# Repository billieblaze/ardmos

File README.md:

ardmos
======

an Arduino Musical Device Operating System

So, I've got this idea for a totally modular synth / controller / whatever environment.   A master ATMega runs an event driven framework and manages any time sensitive operations.   It delegates tasks to a series of "modules" like Digitial IO, Analog IO, MIDI, Matrix LED, etc. Rather then connecting the master straight to a shift register chain, or some other peripherals,  the functionality would be controlled by an i2c ATtiny slave.   

Why would I want to do this?  Well, I've got several musical related projects (Midi sequencer, wavetable oscillator, midi controllers) and I'd like to reign in the codebase a little.  Each project has many similarities that could easily be abstracted.  I feel the advantages are huge for a few reasons:   

1) UI and other long running tasks don't tie up the more crucial time sensitive bits
2) Modules could become their own standalone gizmos or could be interconnected in almost limitless ways

As with many of my projects, I will be standing on the shoulders of giants and utilizing well documented open source libraries and tools and will keep track of that info here as well. 

Proposed Core functionality:
 - Event Driven framework or RTOS
 - MIDI IO with thru / clock sync / clock gen
 - Bootload slaves via I2c using TinySafeBoot (http://jtxp.org/tech/tinysafeboot_en.htm)
 - Allow configuration of slave address / role 

Modules will have an address and a corresponding role.   A simple messaging setup should allow a few bits
to delegate any task and value from the core to the slave.  

In Progress: 
	SuperIO
	- RGB LED Matrix (standard matrix or sparkfun rgb button pad) - TLC5940 + 74hc164 + tlc59213 for led  and 74hc165 for keypad in  
      I'd like to look at the monome protocol for communicating with it since thats already defined, but the device should be able to be independant of pc! 
	- Digital In (button / encoders) 
	- Digital Out (led / trigger / etc)

Other Proposed modules for V1:
	- Analog In  (rot ary pots, audio, cv, etc)  -- todo: select mux
	- Analog Out  (i2c dac, audio / cv)   -- Max525/5250?  
	- I2c text and graphical lcds - these are probably going to wind up being attached to the master, but i've had i2c led related problems in some of my other sketches
	- communication with other platforms (arm / propeller / etc)

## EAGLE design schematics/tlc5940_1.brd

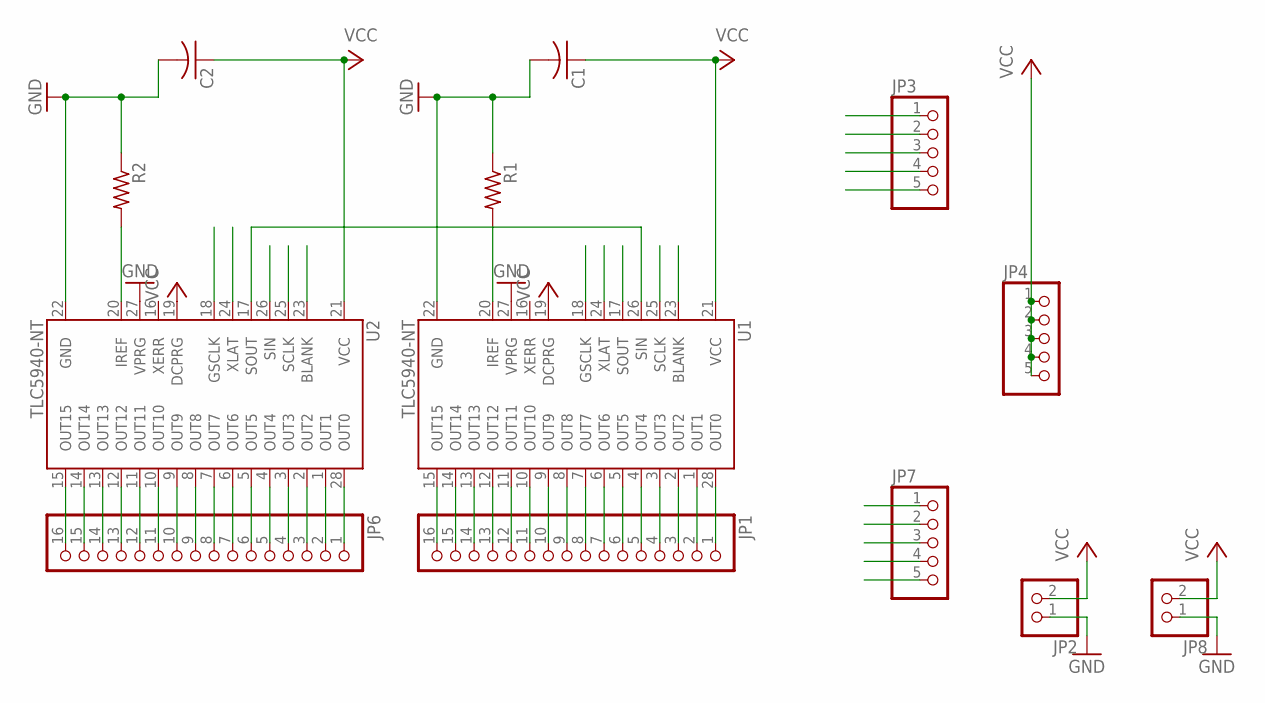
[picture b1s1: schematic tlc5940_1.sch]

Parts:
C1, C2: C-US025-024X044; C025-024X044
JP1, JP6: PINHD-1X16; 1X16
JP2, JP8: PINHD-1X2; 1X02
JP3, JP4, JP7: PINHD-1X5; 1X05
R1, R2: R-US_0613/5V; P0613V
U1, U2: TLC5940-NT; DIL28-3

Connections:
BLANK: JP3.5, JP7.5, U1.23 (BLANK), U2.23 (BLANK)
GND: C1.2, C2.2, JP2.1, JP8.1, R1.1, R2.1, U1.22 (GND), U1.27 (VPRG), U2.22 (GND), U2.27 (VPRG)
GSCLK: JP3.1, JP7.1, U1.18 (GSCLK), U2.18 (GSCLK)
unnamed: JP1.1, U1.28 (OUT0)
unnamed: JP1.2, U1.1 (OUT1)
unnamed: JP1.3, U1.2 (OUT2)
unnamed: JP1.4, U1.3 (OUT3)
unnamed: JP1.5, U1.4 (OUT4)
unnamed: JP1.6, U1.5 (OUT5)
unnamed: JP1.7, U1.6 (OUT6)
unnamed: JP1.8, U1.7 (OUT7)
unnamed: JP1.9, U1.8 (OUT8)
unnamed: JP1.10, U1.9 (OUT9)
unnamed: JP1.11, U1.10 (OUT10)
unnamed: JP1.12, U1.11 (OUT11)
unnamed: JP1.13, U1.12 (OUT12)
unnamed: JP1.14, U1.13 (OUT13)
unnamed: JP1.15, U1.14 (OUT14)
unnamed: JP1.16, U1.15 (OUT15)
unnamed: R1.2, U1.20 (IREF)
unnamed: U1.26 (SIN), U2.17 (SOUT)
unnamed: JP6.1, U2.28 (OUT0)
unnamed: JP6.2, U2.1 (OUT1)
unnamed: JP6.3, U2.2 (OUT2)
unnamed: JP6.4, U2.3 (OUT3)
unnamed: JP6.5, U2.4 (OUT4)
unnamed: JP6.6, U2.5 (OUT5)
unnamed: JP6.7, U2.6 (OUT6)
unnamed: JP6.8, U2.7 (OUT7)
unnamed: JP6.9, U2.8 (OUT8)
unnamed: JP6.10, U2.9 (OUT9)
unnamed: JP6.11, U2.10 (OUT10)
unnamed: JP6.12, U2.11 (OUT11)
unnamed: JP6.13, U2.12 (OUT12)
unnamed: JP6.14, U2.13 (OUT13)
unnamed: JP6.15, U2.14 (OUT14)
unnamed: JP6.16, U2.15 (OUT15)
unnamed: R2.2, U2.20 (IREF)
SCLK: JP3.4, JP7.4, U1.25 (SCLK), U2.25 (SCLK)
SIN: JP3.3, U2.26 (SIN)
SOUT: JP7.3, U1.17 (SOUT)
VCC: C1.1, C2.1, JP2.2, JP4.1, JP4.2, JP4.3, JP4.4, JP4.5, JP8.2, U1.19 (DCPRG), U1.21 (VCC), U2.19 (DCPRG), U2.21 (VCC)
XLAT: JP3.2, JP7.2, U1.24 (XLAT), U2.24 (XLAT)

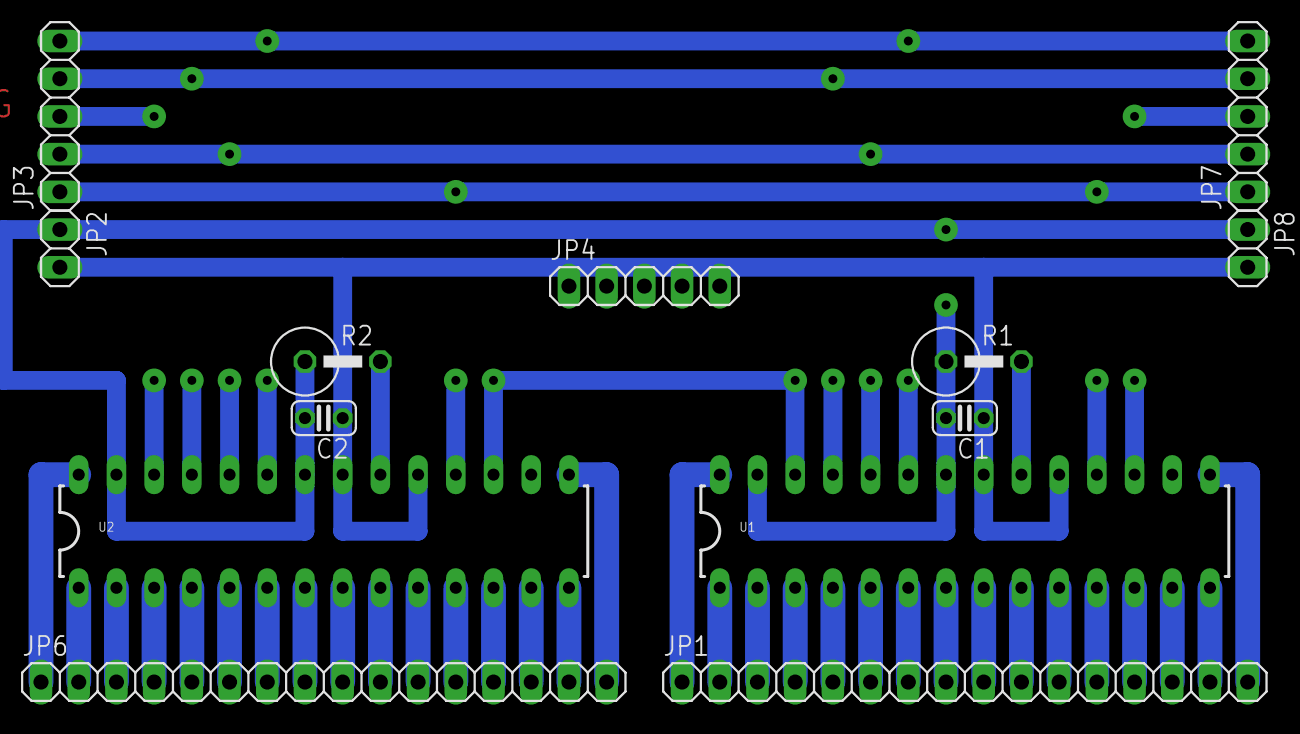
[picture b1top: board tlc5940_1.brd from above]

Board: 2 copper layers, 13 parts (0 on the bottom side), 43 nets.

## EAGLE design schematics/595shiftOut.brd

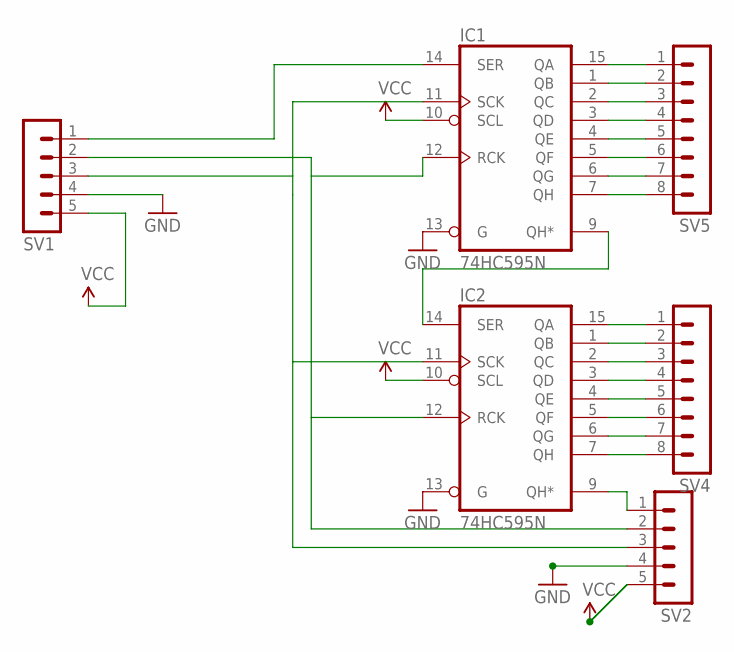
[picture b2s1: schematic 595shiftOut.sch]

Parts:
IC1, IC2: 74HC595N; DIL16
SV1, SV2: MA05-1
SV4, SV5: MA08-1

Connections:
GND: IC1.8 (GND), IC1.13 (G), IC2.8 (GND), IC2.13 (G), SV1.4, SV2.4
unnamed: IC1.14 (SER), SV1.1
unnamed: IC1.12 (RCK), IC2.12 (RCK), SV1.2, SV2.2
unnamed: IC1.11 (SCK), IC2.11 (SCK), SV1.3, SV2.3
unnamed: IC2.15 (QA), SV4.1
unnamed: IC2.1 (QB), SV4.2
unnamed: IC2.2 (QC), SV4.3
unnamed: IC2.3 (QD), SV4.4
unnamed: IC2.4 (QE), SV4.5
unnamed: IC2.5 (QF), SV4.6
unnamed: IC2.6 (QG), SV4.7
unnamed: IC2.7 (QH), SV4.8
unnamed: IC1.15 (QA), SV5.1
unnamed: IC1.1 (QB), SV5.2
unnamed: IC1.2 (QC), SV5.3
unnamed: IC1.3 (QD), SV5.4
unnamed: IC1.4 (QE), SV5.5
unnamed: IC1.5 (QF), SV5.6
unnamed: IC1.6 (QG), SV5.7
unnamed: IC1.7 (QH), SV5.8
unnamed: IC1.9 (QH*), IC2.14 (SER)
unnamed: IC2.9 (QH*), SV2.1
VCC: IC1.10 (SCL), IC1.16 (VCC), IC2.10 (SCL), IC2.16 (VCC), SV1.5, SV2.5

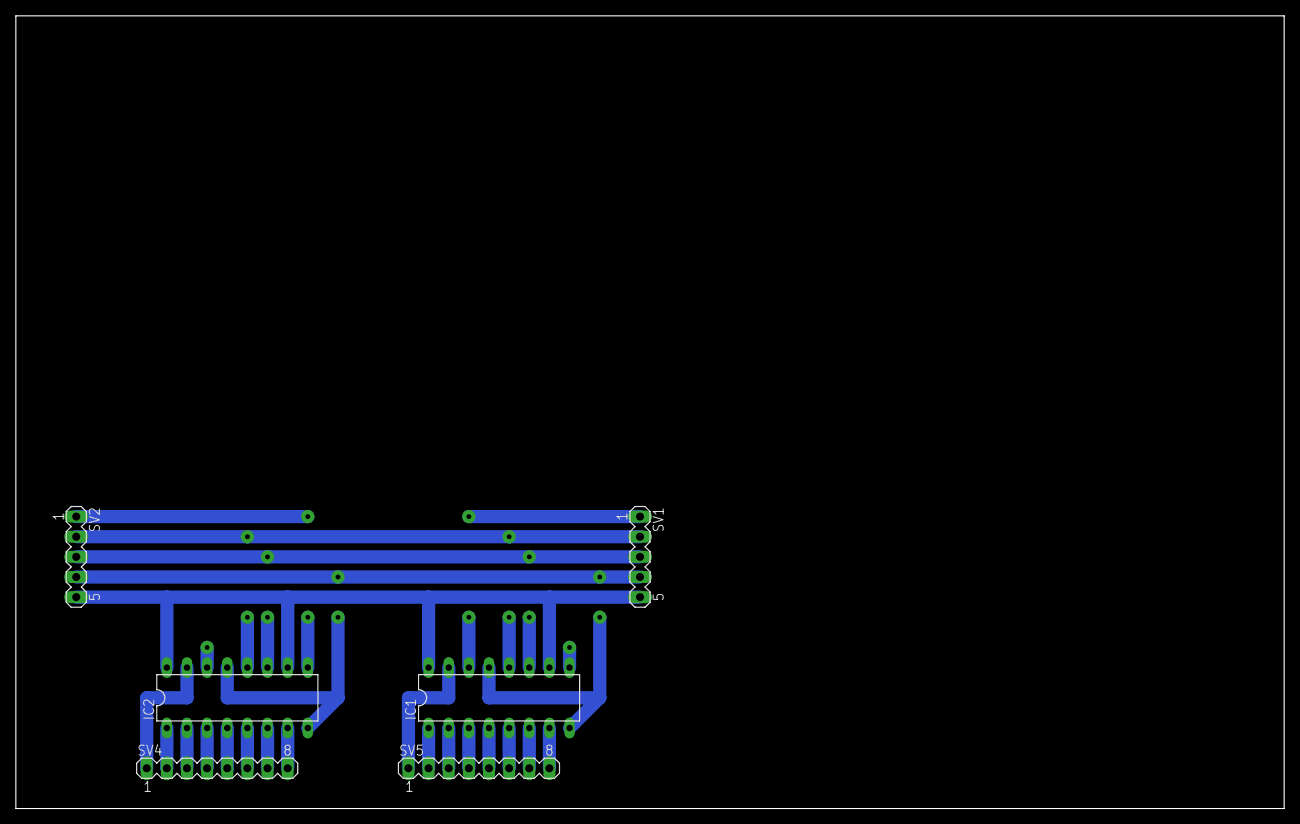
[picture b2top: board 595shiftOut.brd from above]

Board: 2 copper layers, 160.0 x 100.0 mm, 6 parts (0 on the bottom side), 23 nets.

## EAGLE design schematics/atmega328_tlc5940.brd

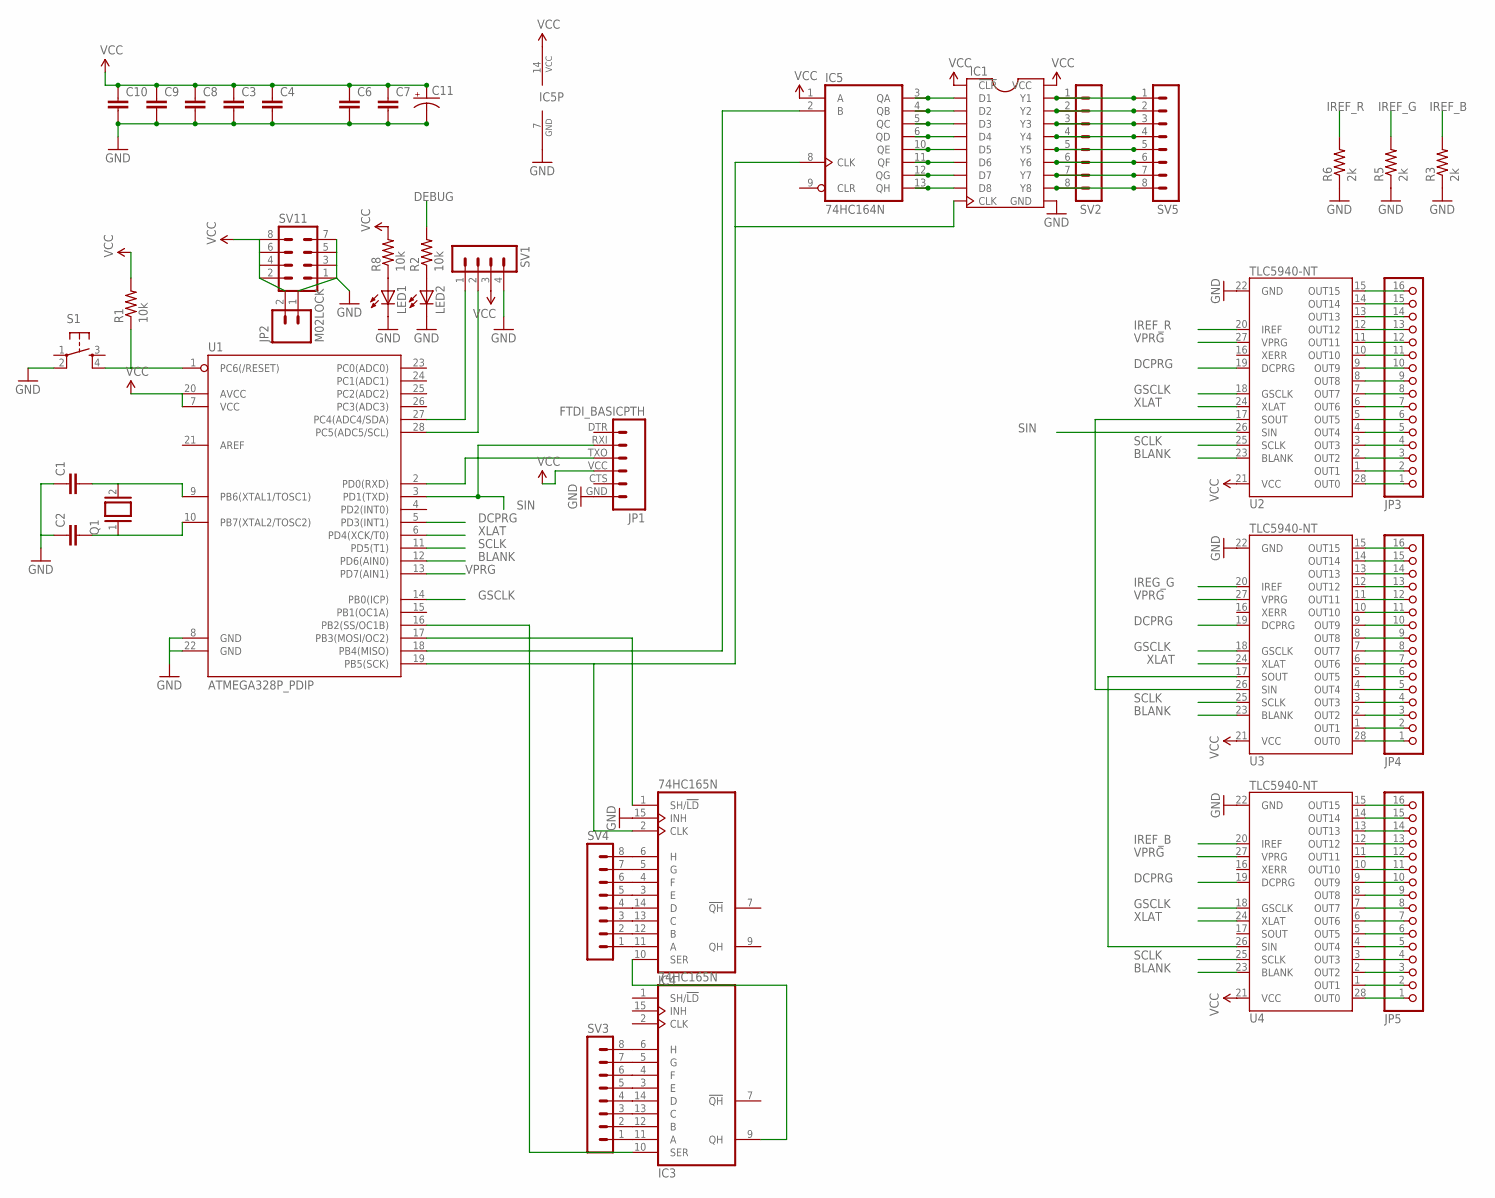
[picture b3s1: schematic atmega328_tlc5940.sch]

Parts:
C1, C2, C3, C4, C6, C7, C8, C9, C10: CAPEZ; CAP-PTH-SMALLEZ
C11: CPOL-USE3.5-8; E3,5-8
IC1: IC-PACKAGE_DIL20S; IC-PACKAGE_SOCKET-20
IC3, IC4: 74HC165N; DIL16
IC5: 74HC164N; DIL14
JP1: FTDI_BASICPTH; FTDI_BASIC
JP2: M02LOCK; 1X02_LOCK
JP3, JP4, JP5: PINHD-1X16; 1X16
LED1, LED2: LED5MM
Q1: XTAL/S; QS
R1, R2, R8: 10k; AXIAL-0.3-KIT
R3, R5, R6: 2k; AXIAL-0.3-KIT
S1: TAC_SWITCHPTH; TACTILE-PTH
SV1: MA04-1
SV2, SV3, SV4, SV5: MA08-1
SV11: MA04-2
U1: ATMEGA328P_PDIP; DIL28-3
U2, U3, U4: TLC5940-NT; DIL28-3

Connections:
BLANK: U1.12 (PD6(AIN0)), U2.23 (BLANK), U3.23 (BLANK), U4.23 (BLANK)
DCPRG: U1.5 (PD3(INT1)), U2.19 (DCPRG), U3.19 (DCPRG), U4.19 (DCPRG)
DEBUG: R2.P$2 (2)
GND: C1.1, C2.1, C3.2, C4.2, C6.2, C7.2, C8.2, C9.2, C10.2, C11.-, IC1.11 (GND), IC3.8 (GND), IC4.8 (GND), IC4.15 (INH), IC5.7 (GND), JP1.GND (6), JP2.1, LED1.K (C), LED2.K (C), R3.P$1 (1), R5.P$1 (1), R6.P$1 (1), S1.2, SV1.4, SV11.1, SV11.3, SV11.5, SV11.7, U1.8 (GND), U1.22 (GND), U2.22 (GND), U3.22 (GND), U4.22 (GND)
GSCLK: U1.14 (PB0(ICP)), U2.18 (GSCLK), U3.18 (GSCLK), U4.18 (GSCLK)
IREF_B: R3.P$2 (2), U4.20 (IREF)
IREF_G: R5.P$2 (2)
IREF_R: R6.P$2 (2), U2.20 (IREF)
IREG_G: U3.20 (IREF)
unnamed: R1.P$1 (1), S1.4, U1.1 (PC6(/RESET))
unnamed: C1.2, Q1.2, U1.9 (PB6(XTAL1/TOSC1))
unnamed: C2.2, Q1.1, U1.10 (PB7(XTAL2/TOSC2))
unnamed: JP3.16, U2.15 (OUT15)
unnamed: JP3.15, U2.14 (OUT14)
unnamed: JP3.14, U2.13 (OUT13)
unnamed: JP3.13, U2.12 (OUT12)
unnamed: JP3.12, U2.11 (OUT11)
unnamed: JP3.11, U2.10 (OUT10)
unnamed: JP3.10, U2.9 (OUT9)
unnamed: JP3.9, U2.8 (OUT8)
unnamed: JP3.8, U2.7 (OUT7)
unnamed: JP3.7, U2.6 (OUT6)
unnamed: JP3.6, U2.5 (OUT5)
unnamed: JP3.5, U2.4 (OUT4)
unnamed: JP3.4, U2.3 (OUT3)
unnamed: JP3.3, U2.2 (OUT2)
unnamed: JP3.2, U2.1 (OUT1)
unnamed: JP3.1, U2.28 (OUT0)
unnamed: JP4.16, U3.15 (OUT15)
unnamed: JP4.15, U3.14 (OUT14)
unnamed: JP4.14, U3.13 (OUT13)
unnamed: SV1.1, U1.27 (PC4(ADC4/SDA))
unnamed: JP4.13, U3.12 (OUT12)
unnamed: JP4.12, U3.11 (OUT11)
unnamed: JP4.11, U3.10 (OUT10)
unnamed: JP4.10, U3.9 (OUT9)
unnamed: JP4.9, U3.8 (OUT8)
unnamed: JP4.8, U3.7 (OUT7)
unnamed: JP4.7, U3.6 (OUT6)
unnamed: JP4.6, U3.5 (OUT5)
unnamed: JP4.5, U3.4 (OUT4)
unnamed: JP4.4, U3.3 (OUT3)
unnamed: JP4.3, U3.2 (OUT2)
unnamed: JP4.2, U3.1 (OUT1)
unnamed: JP4.1, U3.28 (OUT0)
unnamed: JP5.16, U4.15 (OUT15)
unnamed: JP5.15, U4.14 (OUT14)
unnamed: JP5.14, U4.13 (OUT13)
unnamed: JP5.13, U4.12 (OUT12)
unnamed: JP5.12, U4.11 (OUT11)
unnamed: JP5.11, U4.10 (OUT10)
unnamed: JP5.10, U4.9 (OUT9)
unnamed: JP5.9, U4.8 (OUT8)
unnamed: JP5.8, U4.7 (OUT7)
unnamed: JP5.7, U4.6 (OUT6)
unnamed: JP5.6, U4.5 (OUT5)
unnamed: JP5.5, U4.4 (OUT4)
unnamed: JP5.4, U4.3 (OUT3)
unnamed: JP5.3, U4.2 (OUT2)
unnamed: JP5.2, U4.1 (OUT1)
unnamed: JP5.1, U4.28 (OUT0)
unnamed: U2.17 (SOUT), U3.26 (SIN)
unnamed: U3.17 (SOUT), U4.26 (SIN)
unnamed: LED2.A, R2.P$1 (1)
unnamed: LED1.A, R8.P$1 (1)
unnamed: SV1.2, U1.28 (PC5(ADC5/SCL))
unnamed: IC1.2 (D1), IC5.3 (QA)
unnamed: IC5.2 (B), U1.18 (PB4(MISO))
unnamed: IC1.10 (CLK), IC4.2 (CLK), IC5.8 (CLK), U1.19 (PB5(SCK))
unnamed: IC4.1 (SH/!LD), U1.17 (PB3(MOSI/OC2))
unnamed: IC1.3 (D2), IC5.4 (QB)
unnamed: IC1.4 (D3), IC5.5 (QC)
unnamed: IC1.5 (D4), IC5.6 (QD)
unnamed: IC1.6 (D5), IC5.10 (QE)
unnamed: IC1.7 (D6), IC5.11 (QF)
unnamed: IC1.8 (D7), IC5.12 (QG)
unnamed: IC1.9 (D8), IC5.13 (QH)
unnamed: IC3.9 (QH), IC4.10 (SER)
unnamed: IC3.10 (SER), U1.16 (PB2(SS/OC1B))
unnamed: IC1.19 (Y1), SV2.1, SV5.1
unnamed: IC1.18 (Y2), SV2.2, SV5.2
unnamed: IC1.17 (Y3), SV2.3, SV5.3
unnamed: IC1.16 (Y4), SV2.4, SV5.4
unnamed: IC1.15 (Y5), SV2.5, SV5.5
unnamed: IC1.14 (Y6), SV2.6, SV5.6
unnamed: IC1.13 (Y7), SV2.7, SV5.7
unnamed: IC1.12 (Y8), SV2.8, SV5.8
unnamed: IC3.11 (A), SV3.1
unnamed: IC3.12 (B), SV3.2
unnamed: IC3.13 (C), SV3.3
unnamed: IC3.14 (D), SV3.4
unnamed: IC3.3 (E), SV3.5
unnamed: IC3.4 (F), SV3.6
unnamed: IC3.5 (G), SV3.7
unnamed: IC3.6 (H), SV3.8
unnamed: IC4.11 (A), SV4.1
unnamed: IC4.12 (B), SV4.2
unnamed: IC4.13 (C), SV4.3
unnamed: IC4.14 (D), SV4.4
unnamed: IC4.3 (E), SV4.5
unnamed: IC4.4 (F), SV4.6
unnamed: IC4.5 (G), SV4.7
unnamed: IC4.6 (H), SV4.8
RX$0: JP1.TXO (3), U1.2 (PD0(RXD))
SCLK: U1.11 (PD5(T1)), U2.25 (SCLK), U3.25 (SCLK), U4.25 (SCLK)
SIN: JP1.RXI (2), U1.3 (PD1(TXD)), U2.26 (SIN)
VCC: C3.1, C4.1, C6.1, C7.1, C8.1, C9.1, C10.1, C11.+, IC1.1 (!CLR), IC1.20 (VCC), IC3.16 (VCC), IC4.16 (VCC), IC5.1 (A), IC5.14 (VCC), JP1.VCC (4), JP2.2, R1.P$2 (2), R8.P$2 (2), SV1.3, SV11.2, SV11.4, SV11.6, SV11.8, U1.7 (VCC), U1.20 (AVCC), U2.21 (VCC), U3.21 (VCC), U4.21 (VCC)
VPRG: U1.13 (PD7(AIN1)), U2.27 (VPRG), U3.27 (VPRG), U4.27 (VPRG)
XLAT: U1.6 (PD4(XCK/T0)), U2.24 (XLAT), U3.24 (XLAT), U4.24 (XLAT)

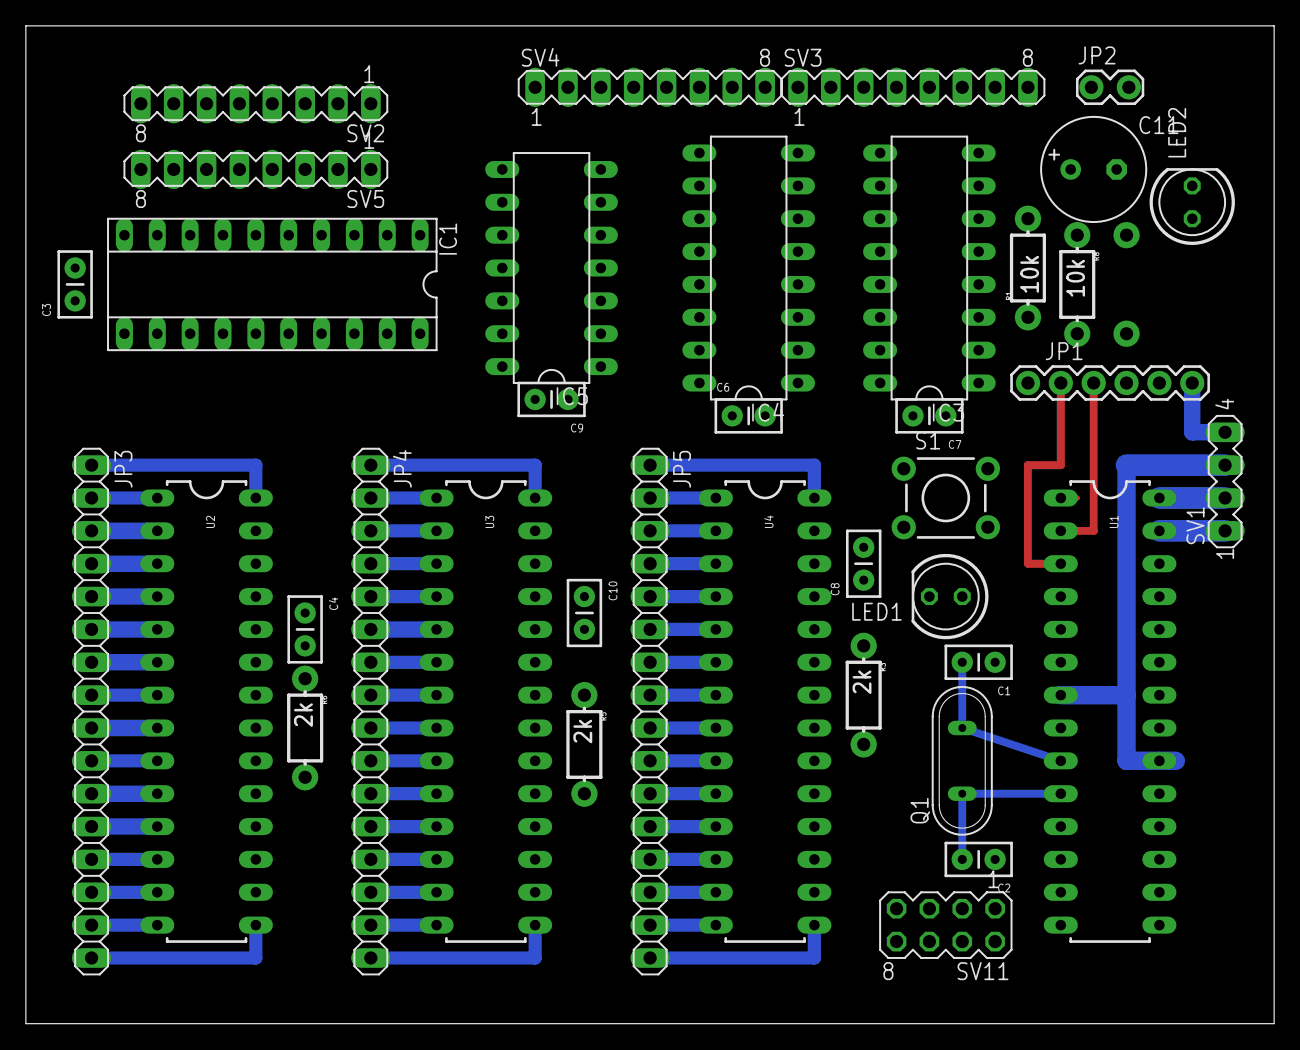
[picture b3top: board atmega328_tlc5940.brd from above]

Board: 2 copper layers, 96.5 x 77.1 mm, 39 parts (1 on the bottom side), 106 nets.

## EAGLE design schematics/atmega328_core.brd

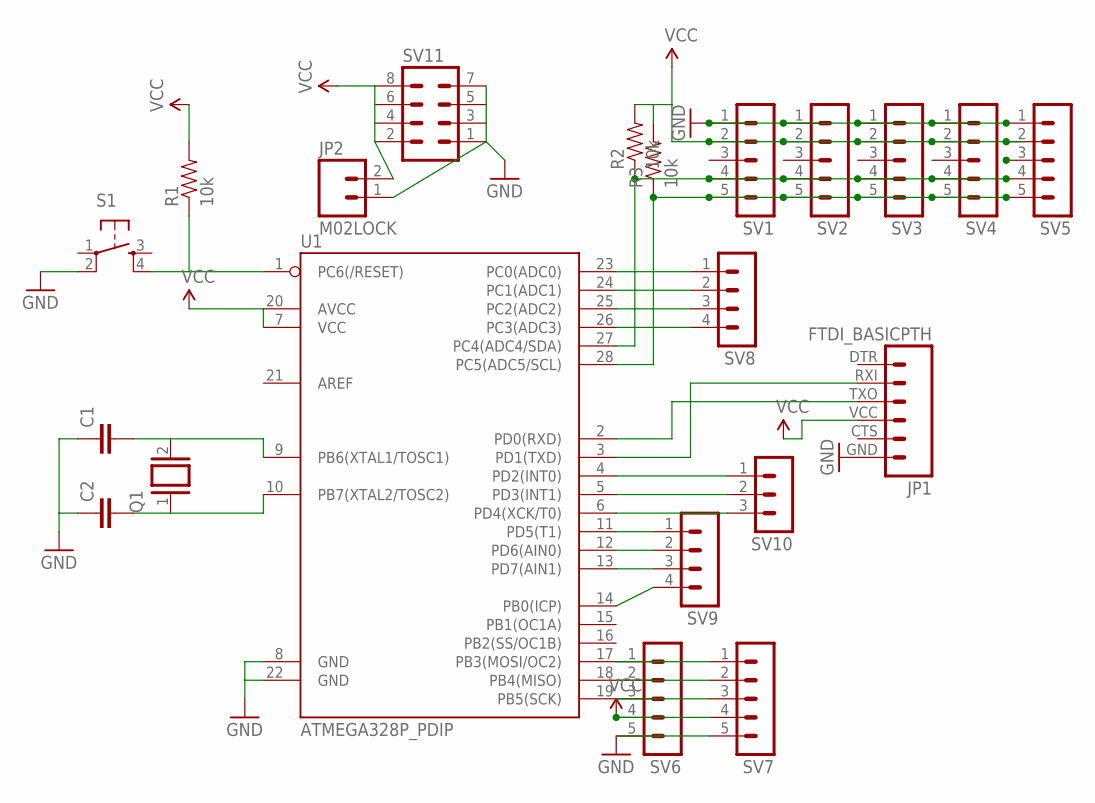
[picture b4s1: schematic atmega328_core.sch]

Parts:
C1, C2: CAPEZ; CAP-PTH-SMALLEZ
JP1: FTDI_BASICPTH; FTDI_BASIC
JP2: M02LOCK; 1X02_LOCK
Q1: XTAL/S; QS
R1, R2, R3: 10k; AXIAL-0.3-KIT
S1: TAC_SWITCHPTH; TACTILE-PTH
SV1, SV2, SV3, SV4, SV5, SV6, SV7: MA05-1
SV8, SV9: MA04-1
SV10: MA03-1
SV11: MA04-2
U1: ATMEGA328P_PDIP; DIL28-3

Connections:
GND: C1.1, C2.1, JP1.GND (6), JP2.1, S1.2, SV1.1, SV2.1, SV3.1, SV4.1, SV5.1, SV6.5, SV7.5, SV11.1, SV11.3, SV11.5, SV11.7, U1.8 (GND), U1.22 (GND)
unnamed: R1.P$1 (1), S1.4, U1.1 (PC6(/RESET))
unnamed: C1.2, Q1.2, U1.9 (PB6(XTAL1/TOSC1))
unnamed: C2.2, Q1.1, U1.10 (PB7(XTAL2/TOSC2))
unnamed: R2.P$1 (1), SV1.4, SV2.4, SV3.4, SV4.4, SV5.4, U1.27 (PC4(ADC4/SDA))
unnamed: R3.P$1 (1), SV1.5, SV2.5, SV3.5, SV4.5, SV5.5, U1.28 (PC5(ADC5/SCL))
unnamed: SV6.1, SV7.1, U1.17 (PB3(MOSI/OC2))
unnamed: SV6.2, SV7.2, U1.18 (PB4(MISO))
unnamed: SV6.3, SV7.3, U1.19 (PB5(SCK))
unnamed: SV8.1, U1.23 (PC0(ADC0))
unnamed: SV8.2, U1.24 (PC1(ADC1))
unnamed: SV8.3, U1.25 (PC2(ADC2))
unnamed: SV8.4, U1.26 (PC3(ADC3))
unnamed: SV9.1, U1.11 (PD5(T1))
unnamed: SV9.2, U1.12 (PD6(AIN0))
unnamed: SV9.3, U1.13 (PD7(AIN1))
unnamed: SV9.4, U1.14 (PB0(ICP))
unnamed: SV10.1, U1.4 (PD2(INT0))
unnamed: SV10.2, U1.5 (PD3(INT1))
unnamed: SV10.3, U1.6 (PD4(XCK/T0))
RX$0: JP1.TXO (3), U1.2 (PD0(RXD))
TX$0: JP1.RXI (2), U1.3 (PD1(TXD))
VCC: JP1.VCC (4), JP2.2, R1.P$2 (2), R2.P$2 (2), R3.P$2 (2), SV1.2, SV2.2, SV3.2, SV4.2, SV5.2, SV6.4, SV7.4, SV11.2, SV11.4, SV11.6, SV11.8, U1.7 (VCC), U1.20 (AVCC)

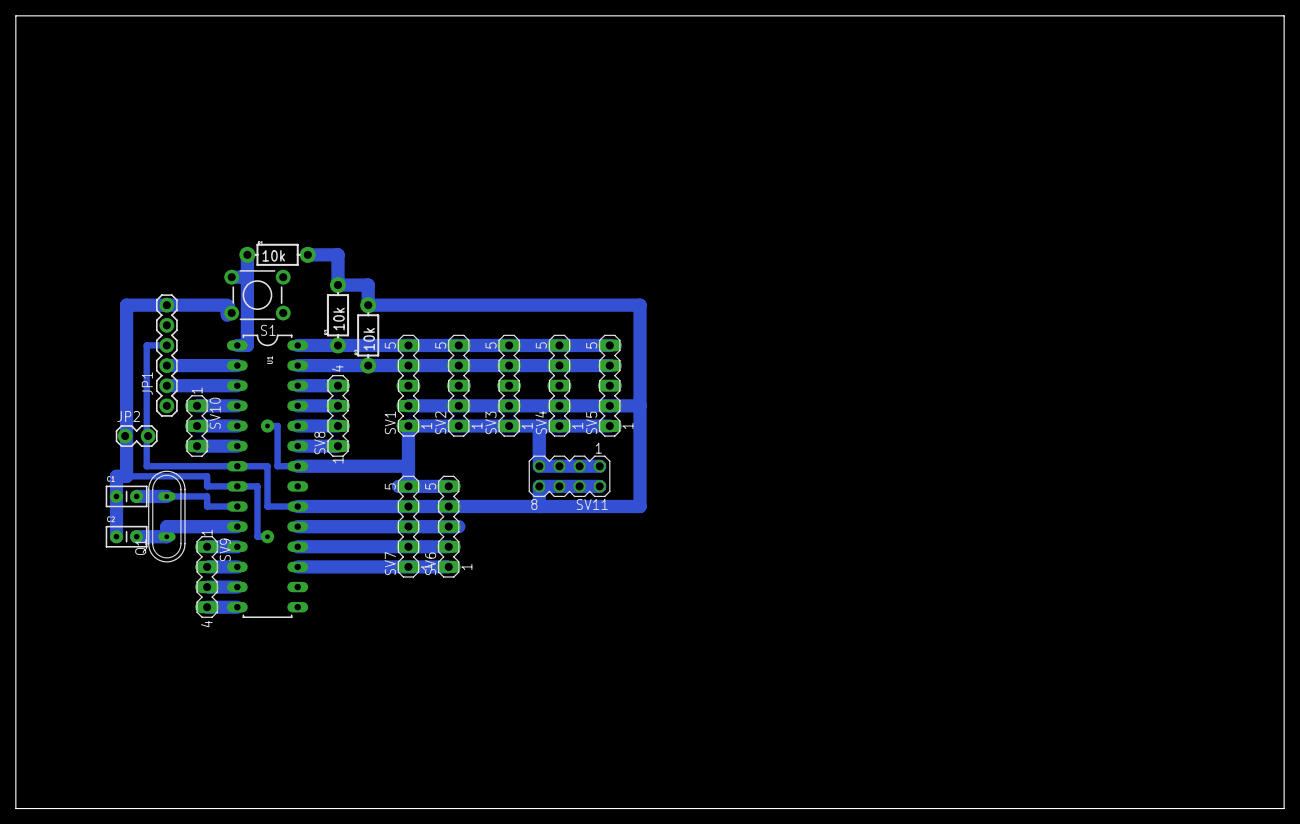
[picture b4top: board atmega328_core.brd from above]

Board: 2 copper layers, 160.0 x 100.0 mm, 21 parts (0 on the bottom side), 23 nets.

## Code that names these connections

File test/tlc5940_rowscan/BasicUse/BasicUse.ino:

/*
    Basic Pin setup:
    ------------                                  ---u----
    ARDUINO   13|-> SCLK (pin 25)           OUT1 |1     28| OUT channel 0
              12|                           OUT2 |2     27|-> GND (VPRG)
              11|-> SIN (pin 26)            OUT3 |3     26|-> SIN (pin 11)
              10|-> BLANK (pin 23)          OUT4 |4     25|-> SCLK (pin 13)
               9|-> XLAT (pin 24)             .  |5     24|-> XLAT (pin 9)
               8|                             .  |6     23|-> BLANK (pin 10)
               7|                             .  |7     22|-> GND
               6|                             .  |8     21|-> VCC (+5V)
               5|                             .  |9     20|-> 2K Resistor -> GND
               4|                             .  |10    19|-> +5V (DCPRG)
               3|-> GSCLK (pin 18)            .  |11    18|-> GSCLK (pin 3)
               2|                             .  |12    17|-> SOUT
               1|                             .  |13    16|-> XERR
               0|                           OUT14|14    15| OUT channel 15
    ------------                                  --------

    -  Put the longer leg (anode) of the LEDs in the +5V and the shorter leg
         (cathode) in OUT(0-15).
    -  +5V from Arduino -> TLC pin 21 and 19     (VCC and DCPRG)
    -  GND from Arduino -> TLC pin 22 and 27     (GND and VPRG)
    -  digital 3        -> TLC pin 18            (GSCLK)
    -  digital 9        -> TLC pin 24            (XLAT)
    -  digital 10       -> TLC pin 23            (BLANK)
    -  digital 11       -> TLC pin 26            (SIN)
    -  digital 13       -> TLC pin 25            (SCLK)
    -  The 2K resistor between TLC pin 20 and GND will let ~20mA through each
       LED.  To be precise, it's I = 39.06 / R (in ohms).  This doesn't depend
       on the LED driving voltage.
    - (Optional): put a pull-up resistor (~10k) between +5V and BLANK so that
                  all the LEDs will turn off when the Arduino is reset.

    If you are daisy-chaining more than one TLC, connect the SOUT of the first
    TLC to the SIN of the next.  All the other pins should just be connected
    together:
        BLANK on Arduino -> BLANK of TLC1 -> BLANK of TLC2 -> ...
        XLAT on Arduino  -> XLAT of TLC1  -> XLAT of TLC2  -> ...
    The one exception is that each TLC needs it's own resistor between pin 20
    and GND.

    This library uses the PWM output ability of digital pins 3, 9, 10, and 11.
    Do not use analogWrite(...) on these pins.

    This sketch does the Knight Rider strobe across a line of LEDs.

    Alex Leone <acleone ~AT~ gmail.com>, 2009-02-03 */

#include "Tlc5940.h"


#define NUM_TLCS 1
#define NUM_ROWS 2


void setup()
{
  /* Call Tlc.init() to setup the tlc.
     You can optionally pass an initial PWM value (0 - 4095) for all channels.*/
  Tlc.init();
  pinMode(A0, LOW);
    digitalWrite(A0, HIGH);

  pinMode(A1, LOW);
    digitalWrite(A1, HIGH);

}

/* This loop will create a Knight Rider-like effect if you have LEDs plugged
   into all the TLC outputs.  NUM_TLCS is defined in "tlc_config.h" in the
   library folder.  After editing tlc_config.h for your setup, delete the
   Tlc5940.o file to save the changes. */
  int row = 0;

void loop()
{
  int direction = 1;
      digitalWrite(A0, HIGH);
      digitalWrite(A1, LOW);
  for ( row = 0; row < NUM_ROWS; row++){

  if ( row == 1){ 
    digitalWrite(A0, LOW);
    digitalWrite(A1, HIGH);
  } else {
Tlc.set(0, 4095);
Tlc.set(4, 4095);
Tlc.set(8, 4095);
Tlc.set(12, 4095);
  }    
  
    for (int channel = 0; channel < NUM_TLCS * 16; channel++) {
    
      /* Tlc.clear() sets all the grayscale values to zero, but does not send
         them to the TLCs.  To actually send the data, call Tlc.update() */
      Tlc.clear();
  
      /* Tlc.set(channel (0-15), value (0-4095)) sets the grayscale value for
         one channel (15 is OUT15 on the first TLC, if multiple TLCs are daisy-
         chained, then channel = 16 would be OUT0 of the second TLC, etc.).
  
         value goes from off (0) to always on (4095).
  
         Like Tlc.clear(), this function only sets up the data, Tlc.update()
         will send the data. */
    
      Tlc.set(channel, 4095);
      if (channel != NUM_TLCS * 16 - 1) {
        Tlc.set(channel + 1, 1000);
      } else {
        direction = -1;
      }
  
      /* Tlc.update() sends the data to the TLCs.  This is when the LEDs will
         actually change. */
      Tlc.update();
      
      delay(150);
    }
  }
}

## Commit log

2014-03-04 initial checkin
2014-03-14 lots of superui schematic / board updates, spectrum analyzer code
2014-03-30 update schematic with row scanning mechanism and tlc5940 pinout changes. clock is shared with all SR's
2015-07-28 rework the schematics for cnc milling
2015-07-28 cleanup eagle files
2015-07-29 pcbgcode the 595

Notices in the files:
parts and their libraries:
SparkFun-Aesthetics: Licensing: CC v3.0 Share-Alike You are welcome to use this library for commercial purposes.
SparkFun-DigitalIC: Licensing: Creative Commons ShareAlike 4.0 International - https://creativecommons.org/licenses/by-sa/4.0
